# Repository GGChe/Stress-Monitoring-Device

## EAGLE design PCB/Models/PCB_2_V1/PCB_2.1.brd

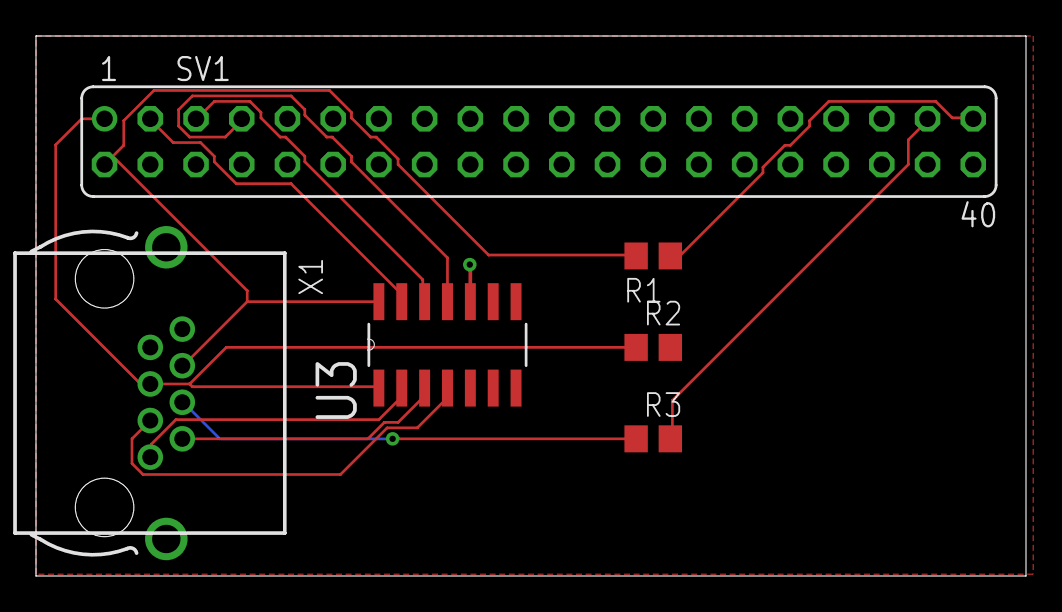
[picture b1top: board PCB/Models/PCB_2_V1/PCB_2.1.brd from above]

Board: 2 copper layers, 55.0 x 30.0 mm, 6 parts (0 on the bottom side), 11 nets.

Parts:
R1, R2, R3: R0805
SV1: FE20-2
U3: TXS0104ED; SOIC127P600X175-14N
X1: 0446200002

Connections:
A1: U3.2, X1.1
A2: U3.3, X1.2
A3: U3.4, X1.3
GND: R1.1, R2.2, SV1.39, U3.5, U3.7, U3.10, X1.8
INT: SV1.7, U3.11
LED: R3.1, X1.4
unnamed: R3.2, SV1.37
SCL: SV1.5, U3.12
SDA: SV1.3, U3.13
VCCA: R2.1, SV1.1, U3.1, X1.5
VCCB: R1.2, SV1.2, U3.14, X1.6

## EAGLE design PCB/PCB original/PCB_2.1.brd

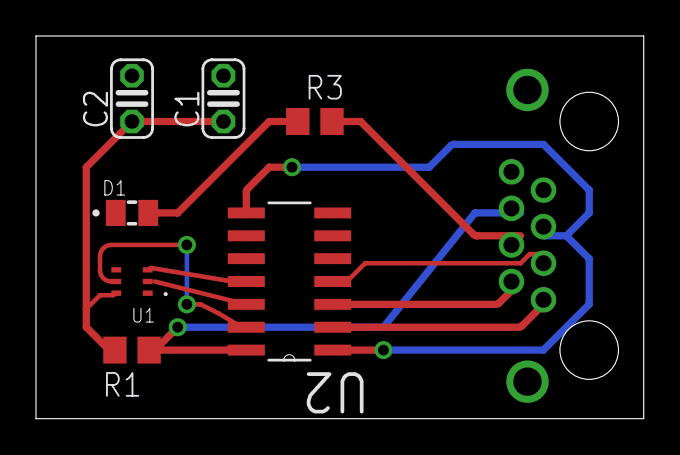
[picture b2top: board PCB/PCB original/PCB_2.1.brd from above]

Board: 2 copper layers, 33.8 x 21.3 mm, 8 parts (1 on the bottom side), 11 nets.

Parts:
C1, C2: C025-024X044
D1: 5988170107F; LEDC2012X70N
R1, R3: R0805
U1: VEML6030; VISHAY_VEML6030_2X2X0.87
U2: TXS0104ED; SOIC127P600X175-14N
X1: 0446200002

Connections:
unnamed: C1.1, C2.1, R1.2, U1.6
unnamed: U1.5, U2.13
unnamed: U1.3, U2.11
unnamed: U1.2, U2.12
unnamed: D1.A, R3.1
unnamed: U2.2, X1.1
unnamed: U2.3, X1.2
unnamed: U2.4, X1.3
unnamed: R1.1, U2.14, X1.6
unnamed: R3.2, X1.4
unnamed: U2.1, U2.8, X1.5
